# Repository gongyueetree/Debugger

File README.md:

# Debug Studio · CH347 + RP2040

面向 CH347T 四模式硬件与 LA_RP2040 板卡的 Web 下载、调试和测量工作台。包含可独立打开的前端、本机 Python Agent、真实工具后端、演示模式和可选 eve AI 任务助手。

**交付状态：v0.2 开发版。软件测试与六份 RP2040 UF2（V1、V2 各三份）交叉编译已完成，没有连接 CH347 / RP2040 实物进行验收。** 所有真实执行路径都会根据工具退出码、API 返回值和响应长度判定结果，无法连接或缺少依赖时返回错误；不会用演示数据填充真实结果。

## 立即启动

需要 Python 3.10 或更新版本。普通下载、调试和规则助手不需要 Node.js 或模型密钥。

```bash
git clone https://github.com/gongyueetree/Debugger.git
cd Debugger
bash start.sh
```

也可在 GitHub 选择 Code → Download ZIP，解压后按下面的方法启动。

- Windows：解压后双击 `start-windows.bat`。
- macOS / Linux：进入解压目录，执行 `bash start.sh`。
- 首次启动创建 `.venv` 并联网安装 `requirements.txt`。依赖安装失败后，可手动重试 `.venv/bin/python -m pip install -r requirements.txt`（Windows 为 `.venv\Scripts\python.exe`）。
- 自动打开 `http://127.0.0.1:8765` 并通过 URL fragment 完成本次配对，随后清除 fragment。每次服务重启都会生成新配对码。
- 如未自动打开网页，复制终端中的本地地址，点击“连接调试器”并填入本次配对码。
- 在线工作台也能连接此服务；若浏览器限制 HTTPS 页面访问本机 HTTP，直接使用本地网页。不要关闭浏览器安全保护。

仅体验页面、不安装硬件依赖：`python -m bridge.server`。网页默认显示明确标记的演示模式。

启动选项：`python -m bridge.server --port 8765 --no-browser --allow-origin https://your-workbench.example`。来源必须是无路径的精确 origin。

## RP2040 新增功能

- **两种板型**：LA_RP2040 V2（电平转换 1.65–5.5 V、端口保护、16 Pin、兼容官方 Debug Probe 固件，硬件工程和外壳在 [hardware/la-rp2040-v2](hardware/la-rp2040-v2/README.md)）和 V1（3.3 V 直连、12 Pin）。固件各三份，不能混用；V2 逻辑分析深度为 50000 点。V2 尚未打样。
- **MCU 调试 + 串口**：专用 CMSIS-DAP v2 固件，复用网页的 OpenOCD / GDB / UART 工具。
- **8 通道逻辑分析仪**：GP20–GP27，最高配置 20 MSa/s，最多 100000 点，边沿/电平触发、波形缩放、游标、CSV/VCD/PulseView .sr 导出。
- **ADC 数字示波器**：GP26/27/28 中选择一路，最高 500 kSa/s、最多 32768 点，12 bit 原始码、Vpp/RMS、游标、CSV 导出。
- **每种板型三份 UF2**：在「RP2040 固件」页下载，经 BOOTSEL 切换；三个配置不同时运行。完整对应固件源码和许可证一并提供。

输入没有模拟前端或电平转换：信号限定 3.3 V；ADC 输入 0–3.3 V 且不得超过实测参考电压。示波器当前是未校准的单次 ADC 采集，不具备通用示波器的宽输入量程、持续流或硬件模拟触发。详细接线、构建和实板验收见 [docs/RP2040.md](docs/RP2040.md)。RP2040 的 debugprobe 固件不支持 JTAG / SWO，openFPGALoader 继续使用 CH347。

## CH347 功能与要求

| 功能 | 本机后端 | 模式 | 实现范围 |
|---|---|---|---|
| FPGA 扫描、SRAM、配置 Flash | openFPGALoader `ch347_jtag` | 3 | 扫描、文件上传、执行计划、下载日志；实际 FPGA/文件格式以工具支持为准 |
| MCU 烧录与调试 | OpenOCD `ch347` | 3 | STM32F1/F4、RP2040、nRF52、ESP32 配置入口；暂停/继续/单步/复位、寄存器与内存读取、ELF/HEX 烧录；不是全系列兼容承诺 |
| GDB 接入 | OpenOCD | 3 | 本机 `127.0.0.1:3333`；可接 GDB/IDE |
| 串口 | pyserial / HID UART | 0/1/2/3 | 8N1，持续收发、文本与日志；模式 0 可打开两个系统端口；无 UART bootloader 自动下载协议 |
| SPI Flash | flashrom `ch347_spi` | 1 | 识别、备份下载、写入默认校验、独立校验、擦除 |
| I²C | WCH SDK / HID | 1/2 | 100 kHz ACK 扫描、7 bit 地址、1/2 byte 寄存器地址、读写；HID 单事务读 ≤63、寄存器地址与写数据合计 ≤62 bytes |
| SPI 原始事务 | WCH SDK / HID | 1/2 | mode 0–3、MSB first、SCS0、全双工；最多 4096 bytes；选取不高于请求的分频 |
| GPIO | WCH SDK | 3 | GPIO3/5/6 读电平、配置输出；与正在运行的调试/XVC 会话互斥 |
| SVF | OpenOCD | 3 | 单 TAP 链的 SVF 执行，需要 IR 长度与 IDCODE；未实现 BSDL 自动互连测试生成 |
| XVC（实验） | 自带 `bridge.xvc` / pyusb | 3 | 独立 CH347T USB JTAG bitbang，XVC v1.0 getinfo/settck/shift，本机 2542 端口；尚未进行 Vivado/ILA 真机验证 |
| 任务助手 | 本地规则 / 可选 eve | 全部 | 引导工作流，AI 可读取状态和准备计划，不能直接写硬件 |

CH347T 的 PID：模式 0 `55DA`、模式 1 `55DB`、模式 2 `55DC`、模式 3 `55DD`，VID 为 `1A86`。软件模式选择只用于准备任务，实际模式按设备枚举校验。每个系列仅允许连接一个设备，但可同时连接一个 CH347T 与一个 RP2040 并在页面选择；CH347F 的 PID/接口布局未纳入支持。

## 外部工具与驱动

本包不附带厂商 DLL、内核驱动、openFPGALoader、OpenOCD 或 flashrom 的可执行文件。请从各项目/厂商安装适合系统架构的版本，并放入 PATH。

- **openFPGALoader**：`openFPGALoader --list-cables` 应包含 `ch347_jtag`。先运行网页里的 JTAG 扫描。底层使用 libusb；Windows 应按工具文档配置正确的 JTAG USB interface，避免替换 UART interface 的驱动。
- **OpenOCD**：CH347 需要真正包含 `ch347` adapter 的构建；RP2040 使用 `cmsis-dap` bulk adapter；系统发行版的旧版本可能没有。目标脚本需要在它的 scripts 搜索路径中。
- **flashrom**：需要编译进 `ch347_spi` programmer。mode 2 HID 不通过这个 programmer 操作。
- **普通 UART**：安装 WCH 对应串口驱动，使系统枚举 COM / tty 设备。
- **pyusb / XVC**：pyusb 还需要系统 libusb。Linux 按上游文档配置 USB udev 权限；macOS 可用系统包管理器安装 libusb；Windows 需要兼容的 libusb 后端库与接口驱动。
- **HID mode 2**：Python 依赖包含 hidapi 与 ch347api。Linux 需对应 hidraw 权限。macOS 的 HID interface_number 行为没有实物验证；找不到设备时报告失败，不能宣称已跨平台验证。
- **WCH SDK**：用于 mode 1 I²C/SPI 和 mode 3 GPIO。Windows DLL 与 Python 位数必须一致；Linux `.so` 与 CPU 架构必须匹配，并按 WCH 官方说明安装 `/dev/ch34x_pis*` 驱动。

WCH SDK 环境变量示例：

```bash
# Linux，路径以你下载的官方 SDK 和实际节点为准
export CH347_LIBRARY=/absolute/path/libch347.so
export CH347_DEVICE_PATH=/dev/ch34x_pis0
bash start.sh
```

```powershell
# Windows PowerShell
$env:CH347_LIBRARY = 'C:\WCH\CH347DLLA64.dll'
$env:CH347_DEVICE_INDEX = '0'
.\start-windows.bat
```

SDK 动态库名称可能随包变化，请填写实际文件；不自动下载 DLL。Linux WCH 字符设备驱动与 libusb 的接口占用可能冲突，切换后端前应停止占用者。SDK ctypes 绑定分别处理 Windows index 与 Linux fd，并使用 `_pack_=1`、固定宽度整数，SPIConfig 为 20 bytes。

## 推荐验收顺序

1. 不接目标板，分别以四种硬件模式上电；连接工作台，确认 PID、版本、串口与驱动识别结果。
2. UART 用 TX/RX 回环测试；模式 0 的两个端口分别验证。新板的 UART0 复用接线以原理图为准。
3. 使用已知 I²C 器件，只读器件标识；随后在可恢复寄存器测试写入。检查模式 1 / 2 ACK 和返回长度。
4. 用独立测试 Flash 进行识别、完整备份、擦除、写入、再次读回比较 SHA-256。
5. JTAG 在 1 MHz 读取稳定 IDCODE；FPGA 先 SRAM 测试设计，再测试配置 Flash 掉电重载。
6. 对支持的 MCU 测试下载校验、复位、暂停、单步、寄存器、内存与外部 GDB。
7. 最后验证 GPIO 与实验性 XVC；观察实际波形、TDO 时序和 Vivado/ILA 行为。

不能用这个软件补足硬件缺失：+3V3 是输出而不是 VTref；若新版要调试 1.8 V 等目标需对应电平转换和方向设计。CH347T 2.41 无原生 SWD，4.41/5.44 有相关限制；本实现 SWD 保守限制 1 MHz。它不是示波器、逻辑分析仪或自动支持任意 MCU 的通用探针。

## 执行与数据策略

- Agent 仅监听 `127.0.0.1`。API 使用启动时随机 Bearer token，检查 Host 和精确 Origin，阻止外网页跨站调用与 DNS rebinding。
- 文件只传给本机 Agent。最多 64 MiB；内部随机文件名；执行前重新比对 SHA-256。上传文件不能成为任意配置脚本或 shell 命令。
- 所有任务先生成最多 5 分钟有效的计划。改变目标状态的操作需确认；同一个计划重复提交不会再次执行。
- 子进程全部参数化调用、无 shell；目标配置为白名单。总线事务在可终止的独立进程中执行；硬件任务互斥，失败不自动重试。
- 服务重启时把进行中的任务标记为 interrupted，绝不自动重放；目标可能处于部分写入状态，需要读回或校验。
- 文件、备份和最近 200 个任务日志保存在用户目录 `.ch347-studio`。程序不会自动删除固件；需要时在服务停止后由用户清理。历史记录会持久化，当前内存中的文件下载映射在服务重启后失效，文件本体仍留在目录内。
- 串口接收记录保留最近 3000 条；操作日志每任务最近 1500 行。关闭网页不会停止已启动的后台会话；使用“断开并停止会话”或在终端 Ctrl+C。
- 非 AI 路径不发送固件或设备数据到模型。启用 AI 后，用户问题和工具返回的设备状态/计划会发送给配置的模型服务；文件内容仍不作为模型附件发送。

## GDB 示例

在网页启动 MCU 调试后：

```gdb
target extended-remote 127.0.0.1:3333
monitor halt
info registers
x/16wx 0x20000000
```

若在外部 GDB 操作目标，应避免同时点击网页调试控制。自定义目标需要在 `bridge/core.py` 的 TARGETS 白名单中添加经过核实的脚本，并更新前端列表；当前网页不接受任意 OpenOCD 配置文件。

## 可选 AI Agent

普通功能完全不依赖模型。`agent-runtime/` 使用 eve，默认模型保留 scaffold 的 `openai/gpt-6-luna-fast`，工具只有读取状态和准备计划；禁用默认 shell、文件和网页工具。

1. 使用 Node.js 24，在 `agent-runtime` 执行 `npm ci`。
2. 在本机配置可用的 AI Gateway 凭据（如 `AI_GATEWAY_API_KEY`），不要放进网页或提交到仓库。此交付未配置凭据，未执行付费模型调用。
3. 启动 Python Agent 前设置 `CH347_EVE_URL=http://127.0.0.1:2000`。启动 Python Agent 后，从终端获得本次配对码。
4. 在 **eve 所在终端** 设置 `CH347_BRIDGE_URL=http://127.0.0.1:8765` 和 `CH347_BRIDGE_TOKEN=本次配对码`，执行 `npx eve dev --no-ui`。若开发服务器端口不是 2000，更新 CH347_EVE_URL 并重新启动 Python Agent，同时更新 eve 的配对码。
5. 工作台刷新连接状态后显示 “EVE AI · 已配置”。这里只表示环境变量已设置；网络、密钥或模型失败时会明确报错。建议先运行 `npm run typecheck` 和 `npm run build`。

AI 返回的是建议与计划文本；最终仍需到相应模块确认执行。Agent 端模型调用不拥有 `/api/execute` 工具，不能绕过网页确认。

## 代码与测试

```text
dist/                独立网页：HTML / CSS / JavaScript
bridge/server.py     localhost HTTP、配对、CORS、上传与下载
bridge/core.py       计划验证、任务互斥、进程、OpenOCD/FPGA/Flash/UART
bridge/bus.py        WCH SDK ABI 与 HID 总线适配
bridge/xvc.py        实验性 CH347T 原始 USB XVC
agent-runtime/       可选 eve AI Agent，typed tools
requirements.txt     Python 依赖
start.sh             macOS / Linux 启动
start-windows.bat    Windows 启动
tests/               硬件隔离的软件测试
```

运行 `python -m unittest discover -s tests -v`。57 项 Python 测试覆盖 RP2040 采集协议、导出、UF2 校验，以及 CH347 的模式、版本、目标配置、文件完整性、计划确认与去重、子进程失败/取消、鉴权/Origin/Host、XVC 向量分包与 TCP 协议。测试使用受控模拟硬件，不能替代真机验收。

运行 `node --test tests/test_waveform.js` 可执行 4 项波形视图回归测试（测试需要 Node.js）。前端已通过浏览器检查缩放按钮、滚轮缩放、滑杆和波形拖动、游标保留，以及导航、计划生成、演示执行与记录；SHA-256 fallback 使用 4 个标准实现对照向量校验。eve 类型检查与生产构建通过，模型调用未测试。

## 参考来源

- WCH CH347 官方资料：https://www.wch.cn/products/CH347.html
- WCH Linux SDK：https://github.com/WCHSoftGroup/ch341par_linux
- WCH Linux ABI：https://github.com/WCHSoftGroup/ch341par_linux/blob/main/demo/ch347/ch347_lib.h
- openFPGALoader：https://github.com/trabucayre/openFPGALoader
- CH347 USB 协议核对：https://github.com/trabucayre/openFPGALoader/blob/master/src/ch347jtag.cpp
- XVC 支持范围核对：https://github.com/trabucayre/openFPGALoader/blob/master/src/xvc_server.cpp
- OpenOCD：https://github.com/openocd-org/openocd
- flashrom：https://github.com/flashrom/flashrom
- HID Python 实现：https://github.com/i2cy/CH347-HIDAPI

特别说明：openFPGALoader 支持 `ch347_jtag` 下载；经检查其 XVC 构造器尚未接入 CH347，且该实现未使用传入 IP 绑定地址。因此本项目没有直接调用 `openFPGALoader --xvc -c ch347_jtag`，而实现了只监听 loopback 的独立 XVC 后端。HID I²C 加入超时、返回长度与帧检查；HID GPIO 目前未开放。

## 生成完整启动包

```bash
python package_release.py dist/CH347_Debug_Studio.zip
```

这会生成网页“连接设置”中可下载的完整启动包；Git 仓库不重复提交这个生成文件。`dist/firmware/` 已包含三份专用 UF2、版本校验清单和完整对应源码包，克隆后即可使用。

## 工具汇总与硬件可视化

左侧「工具汇总」可下载两块板的原始 KiCad 9 工程，并在线查看带图纸外框和标题栏的原理图、PCB 双层叠加 / 正反面及可旋转的 3D 装配模型。PCB 可点击走线、焊盘或过孔，高亮整个网络并显示名称和连接的管脚。板卡图片与 3D 均保留原始管脚丝印；各功能页显示实际 J2 脚号、板上丝印和当前功能，随 ADC、GPIO、UART 与总线选择更新。详见 [硬件资料与重建说明](docs/HARDWARE.md)。

验证：`python -m unittest discover -s tests -v`（57 项），`node --test tests/test_waveform.js tests/test_hardware.js tests/test_pcb_viewer.js`（13 项）。硬件资料校验包括原文件哈希、正反面焊盘、丝印对应、引脚映射与本地静态资源类型。

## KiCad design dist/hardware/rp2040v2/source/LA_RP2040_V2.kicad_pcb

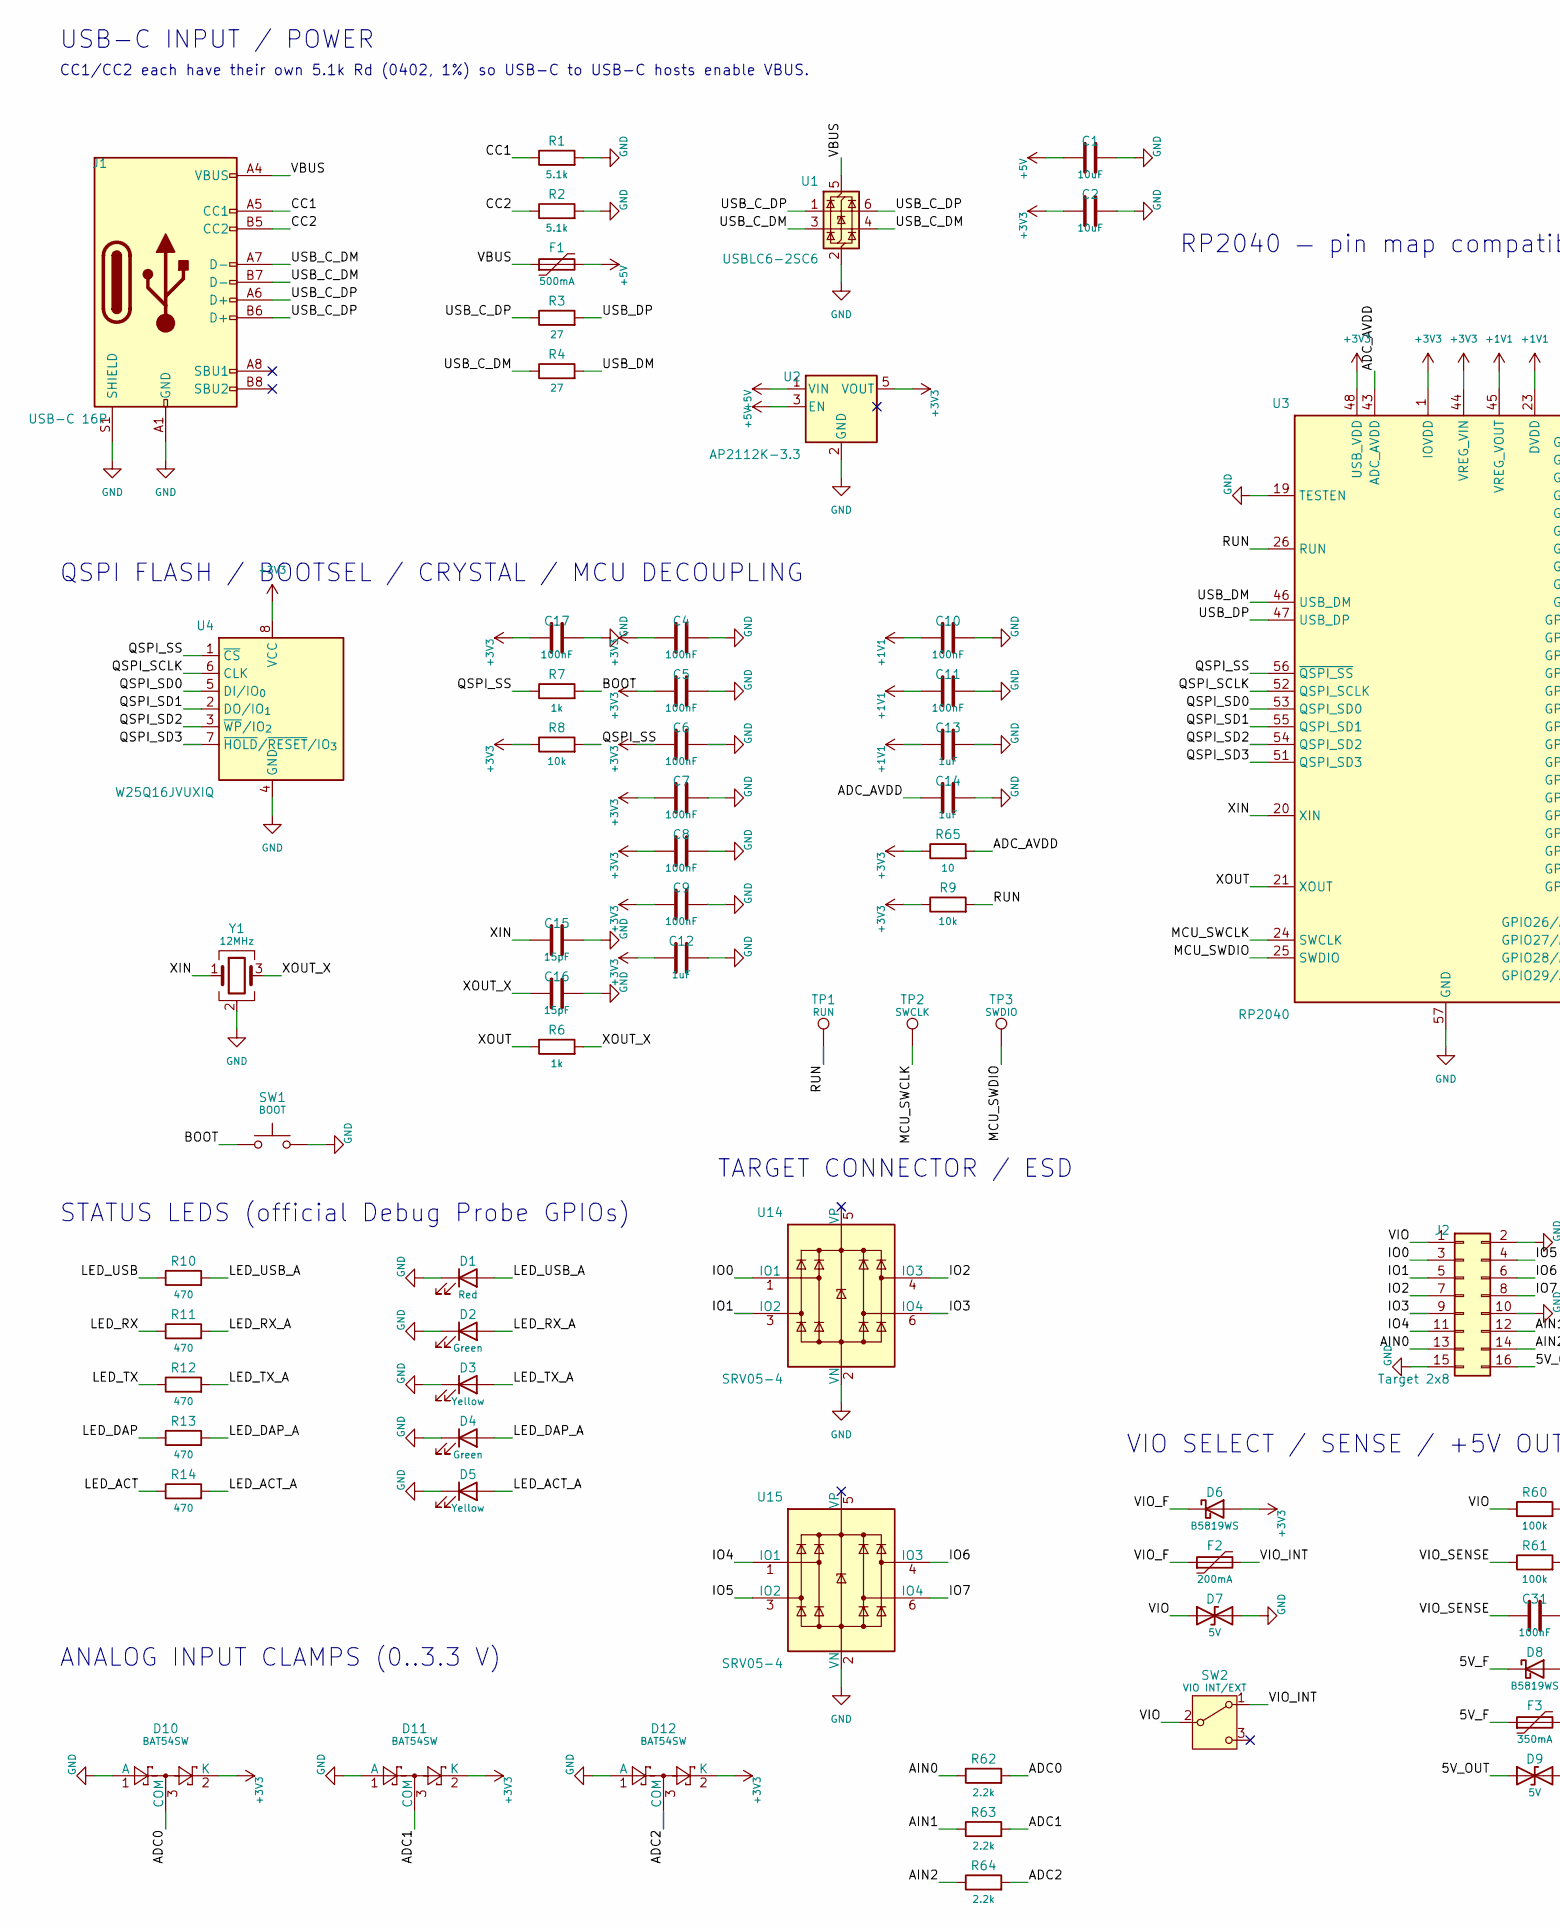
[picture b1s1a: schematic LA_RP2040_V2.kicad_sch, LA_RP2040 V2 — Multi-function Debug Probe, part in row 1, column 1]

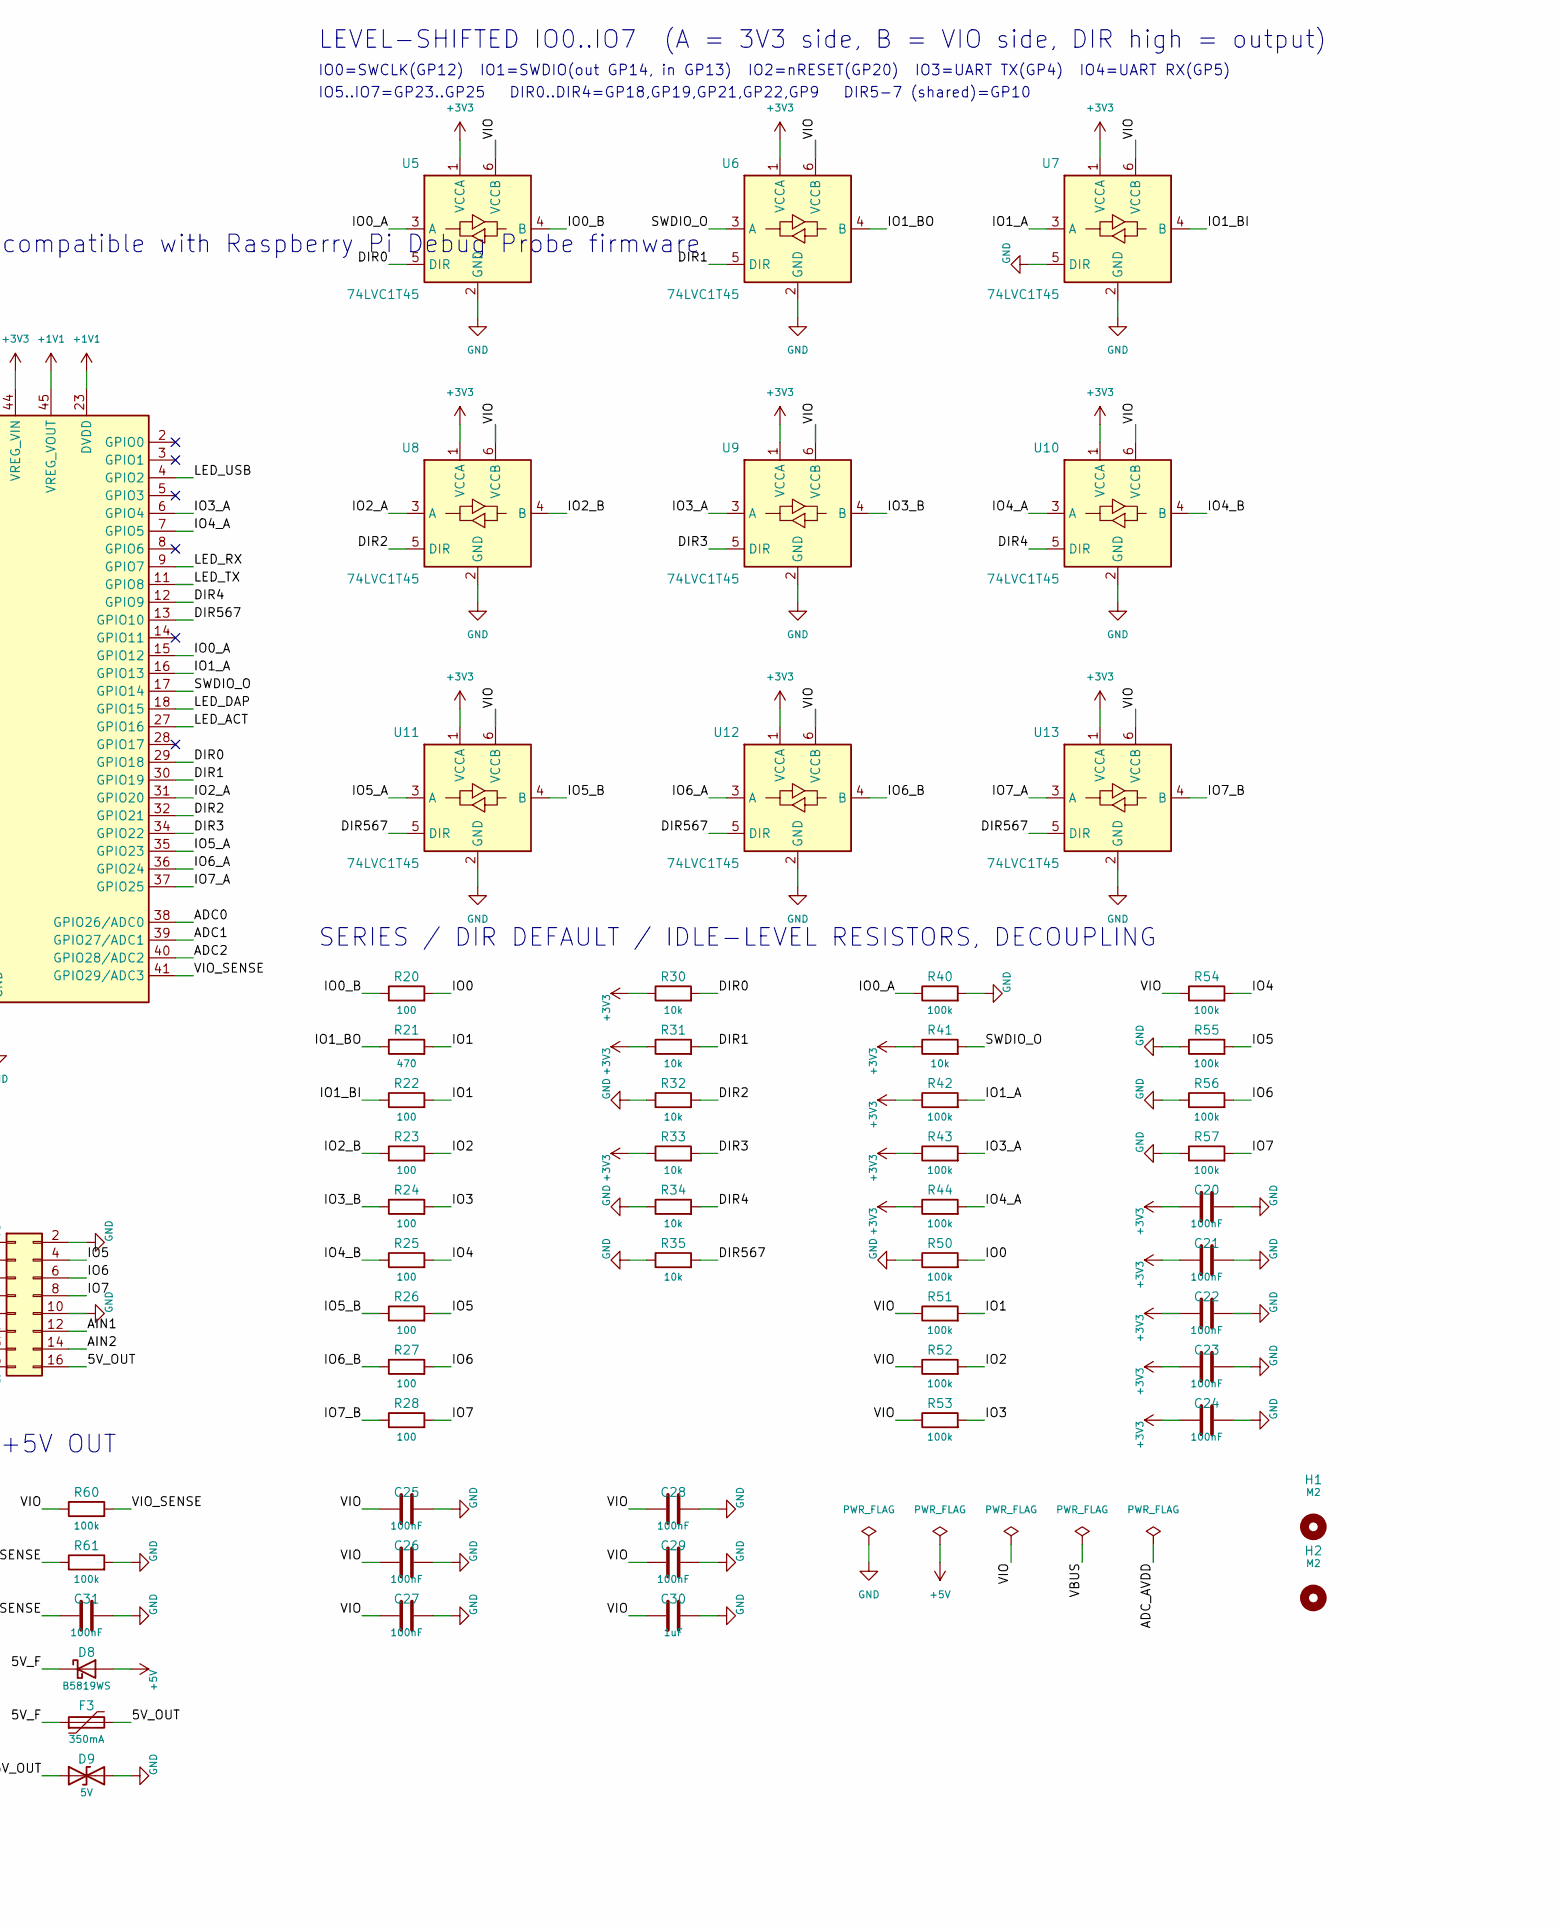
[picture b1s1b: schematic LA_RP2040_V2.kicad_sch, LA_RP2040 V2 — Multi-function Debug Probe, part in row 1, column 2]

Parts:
C1, C2: 10uF; C_0603_1608Metric; MPN 0603 10uF X5R/X7R (15pF: C0G)
C4, C5, C6, C7, C8, C9, C10, C11, C17, C20, C21, C22, C23, C24, C25, C26, C27, C28, C29, C31: 100nF; C_0402_1005Metric; MPN 0402 100nF X5R/X7R (15pF: C0G)
C12, C13, C14, C30: 1uF; C_0402_1005Metric; MPN 0402 1uF X5R/X7R (15pF: C0G)
C15, C16: 15pF; C_0402_1005Metric; MPN 0402 15pF X5R/X7R (15pF: C0G)
D1: Red; LED_0603_1608Metric; MPN 0603 LED Red
D2, D4: Green; LED_0603_1608Metric; MPN 0603 LED Green
D3, D5: Yellow; LED_0603_1608Metric; MPN 0603 LED Yellow
D6, D8: B5819WS; D_SOD-323; MPN B5819WS (SOD-323)
D7, D9: 5V; D_SOD-323; MPN PESD5V0S1BA (SOD-323)
D10, D11, D12: BAT54SW; SOT-323_SC-70; MPN BAT54SW (SOT-323)
F1: 500mA; Fuse_0805_2012Metric; MPN 0805 PTC 0.5A hold / 6V (e.g. SMD0805P0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
F2: 200mA; Fuse_0603_1608Metric; MPN 0603 PTC 0.2A hold / 6V
F3: 350mA; Fuse_0603_1608Metric; MPN 0603 PTC 0.35A hold / 6V
H1, H2: M2; MountingHole_2.2mm_M2
J1: USB-C 16P; USB_C_Receptacle_HRO_TYPE-C-31-M-12; MPN HRO TYPE-C-31-M-12
J2: Target 2x8; PinHeader_2x08_P2.54mm_EdgeMount; MPN 2x8 2.54 mm straight pin header, stradd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
R1, R2: 5.1k; R_0402_1005Metric; MPN 0402 5.1k 1%
R3, R4: 27; R_0402_1005Metric; MPN 0402 27 1%
R6, R7: 1k; R_0402_1005Metric; MPN 0402 1k 1%
R8, R9, R30, R31, R32, R33, R34, R35, R41: 10k; R_0402_1005Metric; MPN 0402 10k 1%
R10, R11, R12, R13, R14, R21: 470; R_0402_1005Metric; MPN 0402 470 1%
R20, R22, R23, R24, R25, R26, R27, R28: 100; R_0402_1005Metric; MPN 0402 100 1%
R40, R42, R43, R44, R50, R51, R52, R53, R54, R55, R56, R57, R60, R61: 100k; R_0402_1005Metric; MPN 0402 100k 1%
R62, R63, R64: 2.2k; R_0402_1005Metric; MPN 0402 2.2k 1%
R65: 10; R_0402_1005Metric; MPN 0402 10 1%
SW1: BOOT; SW_SPST_B3U-1000P; MPN Omron B3U-1000P
SW2: VIO INT/EXT; SW_SPDT_Shouhan_MSK12C02; MPN Shouhan MSK-12C02
TP1: RUN; TestPoint_Pad_D1.0mm
TP2: SWCLK; TestPoint_Pad_D1.0mm
TP3: SWDIO; TestPoint_Pad_D1.0mm
U1: USBLC6-2SC6; SOT-23-6; MPN USBLC6-2SC6
U2: AP2112K-3.3; SOT-23-5; MPN AP2112K-3.3TRG1
U3: RP2040; QFN-56-1EP_7x7mm_P0.4mm_EP3.2x3.2mm; MPN RP2040
U4: W25Q16JVUXIQ; Winbond_USON-8-1EP_3x2mm_P0.5mm_EP0.2x1.6mm; MPN W25Q16JVUXIQ
U5, U6, U7, U8, U9, U10, U11, U12, U13: 74LVC1T45; SOT-363_SC-70-6; MPN SN74LVC1T45DCKR
U14, U15: SRV05-4; SOT-23-6; MPN SRV05-4 (SOT-23-6)
Y1: 12MHz; Crystal_SMD_3225-4Pin_3.2x2.5mm; MPN 12 MHz 3225 CL=10..12pF (e.g. ABM8-272-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

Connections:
+1V1: C10.1, C11.1, C13.1, U3.23 (DVDD), U3.45 (VREG_VOUT), U3.50 (DVDD)
+3V3: C2.1, C4.1, C5.1, C6.1, C7.1, C8.1, C9.1, C12.1, C17.1, C20.1, C21.1, C22.1, C23.1, C24.1, D6.2 (A), D10.2 (K), D11.2 (K), D12.2 (K), R8.1, R9.1, R30.1, R31.1, R33.1, R41.1, R42.1, R43.1, R44.1, R65.1, U2.5 (VOUT), U3.1 (IOVDD), U3.10 (IOVDD), U3.22 (IOVDD), U3.33 (IOVDD), U3.42 (IOVDD), U3.44 (VREG_VIN), U3.48 (USB_VDD), U3.49 (IOVDD), U4.8 (VCC), U5.1 (VCCA), U6.1 (VCCA), U7.1 (VCCA), U8.1 (VCCA), U9.1 (VCCA), U10.1 (VCCA), U11.1 (VCCA), U12.1 (VCCA), U13.1 (VCCA)
+5V: C1.1, D8.2 (A), F1.2, U2.1 (VIN), U2.3 (EN)
/5V_F: D8.1 (K), F3.1
/5V_OUT: D9.1 (A1), F3.2, J2.16
/ADC0: D10.3 (COM), R62.2, U3.38 (GPIO26/ADC0)
/ADC1: D11.3 (COM), R63.2, U3.39 (GPIO27/ADC1)
/ADC2: D12.3 (COM), R64.2, U3.40 (GPIO28/ADC2)
/ADC_AVDD: C14.1, R65.2, U3.43 (ADC_AVDD)
/AIN0: J2.13, R62.1
/AIN1: J2.12, R63.1
/AIN2: J2.14, R64.1
/BOOT: R7.2, SW1.1
/CC1: J1.A5 (CC1), R1.1
/CC2: J1.B5 (CC2), R2.1
/DIR0: R30.2, U3.29 (GPIO18), U5.5 (DIR)
/DIR1: R31.2, U3.30 (GPIO19), U6.5 (DIR)
/DIR2: R32.2, U3.32 (GPIO21), U8.5 (DIR)
/DIR3: R33.2, U3.34 (GPIO22), U9.5 (DIR)
/DIR4: R34.2, U3.12 (GPIO9), U10.5 (DIR)
/DIR567: R35.2, U3.13 (GPIO10), U11.5 (DIR), U12.5 (DIR), U13.5 (DIR)
/IO0: J2.3, R20.2, R50.2, U14.1 (IO1)
/IO0_A: R40.1, U3.15 (GPIO12), U5.3 (A)
/IO0_B: R20.1, U5.4 (B)
/IO1: J2.5, R21.2, R22.2, R51.2, U14.3 (IO2)
/IO1_A: R42.2, U3.16 (GPIO13), U7.3 (A)
/IO1_BI: R22.1, U7.4 (B)
/IO1_BO: R21.1, U6.4 (B)
/IO2: J2.7, R23.2, R52.2, U14.4 (IO3)
/IO2_A: U3.31 (GPIO20), U8.3 (A)
/IO2_B: R23.1, U8.4 (B)
/IO3: J2.9, R24.2, R53.2, U14.6 (IO4)
/IO3_A: R43.2, U3.6 (GPIO4), U9.3 (A)
/IO3_B: R24.1, U9.4 (B)
/IO4: J2.11, R25.2, R54.2, U15.1 (IO1)
/IO4_A: R44.2, U3.7 (GPIO5), U10.3 (A)
/IO4_B: R25.1, U10.4 (B)
/IO5: J2.4, R26.2, R55.2, U15.3 (IO2)
/IO5_A: U3.35 (GPIO23), U11.3 (A)
/IO5_B: R26.1, U11.4 (B)
/IO6: J2.6, R27.2, R56.2, U15.4 (IO3)
/IO6_A: U3.36 (GPIO24), U12.3 (A)
/IO6_B: R27.1, U12.4 (B)
/IO7: J2.8, R28.2, R57.2, U15.6 (IO4)
/IO7_A: U3.37 (GPIO25), U13.3 (A)
/IO7_B: R28.1, U13.4 (B)
/LED_ACT: R14.1, U3.27 (GPIO16)
/LED_ACT_A: D5.2 (A), R14.2
/LED_DAP: R13.1, U3.18 (GPIO15)
/LED_DAP_A: D4.2 (A), R13.2
/LED_RX: R11.1, U3.9 (GPIO7)
/LED_RX_A: D2.2 (A), R11.2
/LED_TX: R12.1, U3.11 (GPIO8)
/LED_TX_A: D3.2 (A), R12.2
/LED_USB: R10.1, U3.4 (GPIO2)
/LED_USB_A: D1.2 (A), R10.2
/MCU_SWCLK: TP2.1, U3.24 (SWCLK)
/MCU_SWDIO: TP3.1, U3.25 (SWDIO)
/QSPI_SCLK: U3.52 (QSPI_SCLK), U4.6 (CLK)
/QSPI_SD0: U3.53 (QSPI_SD0), U4.5 (DI/IO_{0})
/QSPI_SD1: U3.55 (QSPI_SD1), U4.2 (DO/IO_{1})
/QSPI_SD2: U3.54 (QSPI_SD2), U4.3 (~WP/IO_{2})
/QSPI_SD3: U3.51 (QSPI_SD3), U4.7 (~HOLD/~RESET/IO_{3})
/QSPI_SS: R7.1, R8.2, U3.56 (~QSPI_SS), U4.1 (~CS)
/RUN: R9.2, TP1.1, U3.26 (RUN)
/SWDIO_O: R41.2, U3.17 (GPIO14), U6.3 (A)
/USB_C_DM: J1.A7 (D-), J1.B7 (D-), R4.1, U1.3 (I/O2), U1.4 (I/O2)
/USB_C_DP: J1.A6 (D+), J1.B6 (D+), R3.1, U1.1 (I/O1), U1.6 (I/O1)
/USB_DM: R4.2, U3.46 (USB_DM)
/USB_DP: R3.2, U3.47 (USB_DP)
/VBUS: F1.1, J1.A4 (VBUS), J1.A9 (VBUS), J1.B4 (VBUS), J1.B9 (VBUS), U1.5 (VBUS)
/VIO_F: D6.1 (K), F2.1
/VIO_INT: F2.2, SW2.1 (A)
/VIO_SENSE: C31.1, R60.2, R61.1, U3.41 (GPIO29/ADC3)
/XIN: C15.1, U3.20 (XIN), Y1.1
/XOUT: R6.1, U3.21 (XOUT)
/XOUT_X: C16.1, R6.2, Y1.3
GND: C1.2, C2.2, C4.2, C5.2, C6.2, C7.2, C8.2, C9.2, C10.2, C11.2, C12.2, C13.2, C14.2, C15.2, C16.2, C17.2, C20.2, C21.2, C22.2, C23.2, C24.2, C25.2, C26.2, C27.2, C28.2, C29.2, C30.2, C31.2, D1.1 (K), D2.1 (K), D3.1 (K), D4.1 (K), D5.1 (K), D7.2 (A2), D9.2 (A2), D10.1 (A), D11.1 (A), D12.1 (A), J1.A1 (GND), J1.A12 (GND), J1.B1 (GND), J1.B12 (GND), J1.S1 (SHIELD), J2.2, J2.10, J2.15, R1.2, R2.2, R32.1, R34.1, R35.1, R40.2, R50.1, R55.1, R56.1, R57.1, R61.2, SW1.2, U1.2 (GND), U2.2 (GND), U3.19 (TESTEN), U3.57 (GND), U4.4 (GND), U5.2 (GND), U6.2 (GND), U7.2 (GND), U7.5 (DIR), U8.2 (GND), U9.2 (GND), U10.2 (GND), U11.2 (GND), U12.2 (GND), U13.2 (GND), U14.2 (VN), U15.2 (VN), Y1.2 (G), Y1.4 (G)
VIO: C25.1, C26.1, C27.1, C28.1, C29.1, C30.1, D7.1 (A1), J2.1, R51.1, R52.1, R53.1, R54.1, R60.1, SW2.2 (B), U5.6 (VCCB), U6.6 (VCCB), U7.6 (VCCB), U8.6 (VCCB), U9.6 (VCCB), U10.6 (VCCB), U11.6 (VCCB), U12.6 (VCCB), U13.6 (VCCB)

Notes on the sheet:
USB-C INPUT / POWER
QSPI FLASH / BOOTSEL / CRYSTAL / MCU DECOUPLING
STATUS LEDS (official Debug Probe GPIOs)
RP2040 — pin map compatible with Raspberry Pi Debug Probe firmware
LEVEL-SHIFTED IO0..IO7 (A = 3V3 side, B = VIO side, DIR high = output)
SERIES / DIR DEFAULT / IDLE-LEVEL RESISTORS, DECOUPLING
TARGET CONNECTOR / ESD
VIO SELECT / SENSE / +5V OUT
ANALOG INPUT CLAMPS (0..3.3 V)
IO0=SWCLK(GP12) IO1=SWDIO(out GP14, in GP13) IO2=nRESET(GP20) IO3=UART TX(GP4) IO4=UART RX(GP5)
IO5..IO7=GP23..GP25 DIR0..DIR4=GP18,GP19,GP21,GP22,GP9 DIR5-7 (shared)=GP10
CC1/CC2 each have their own 5.1k Rd (0402, 1%) so USB-C to USB-C hosts enable VBUS.

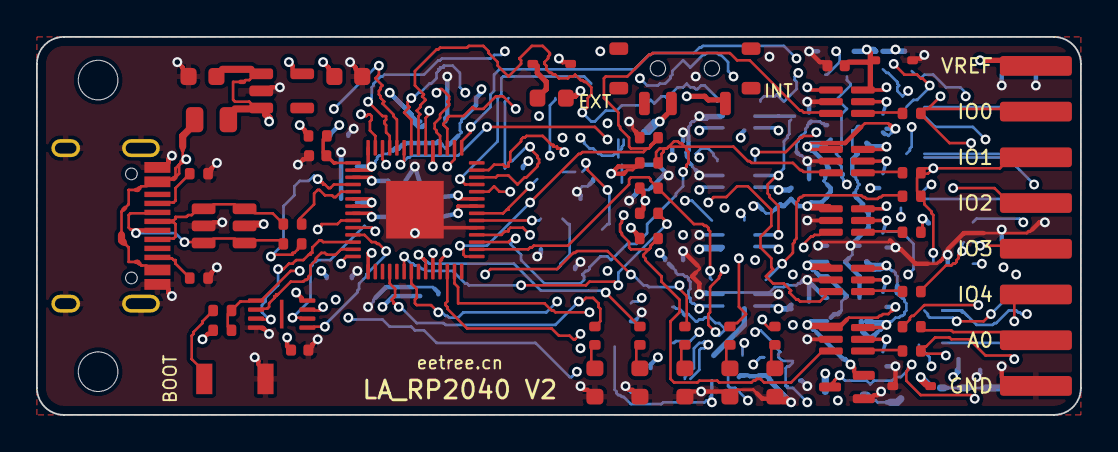
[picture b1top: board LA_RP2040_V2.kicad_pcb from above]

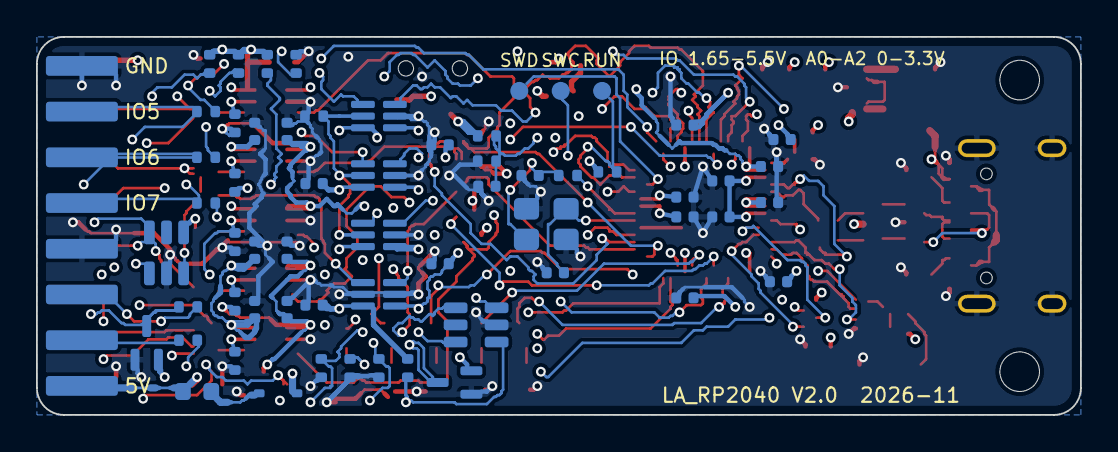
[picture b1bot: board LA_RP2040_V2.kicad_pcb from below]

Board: 4 copper layers, 58.0 x 21.0 mm, 115 parts (60 on the bottom side), 79 nets.

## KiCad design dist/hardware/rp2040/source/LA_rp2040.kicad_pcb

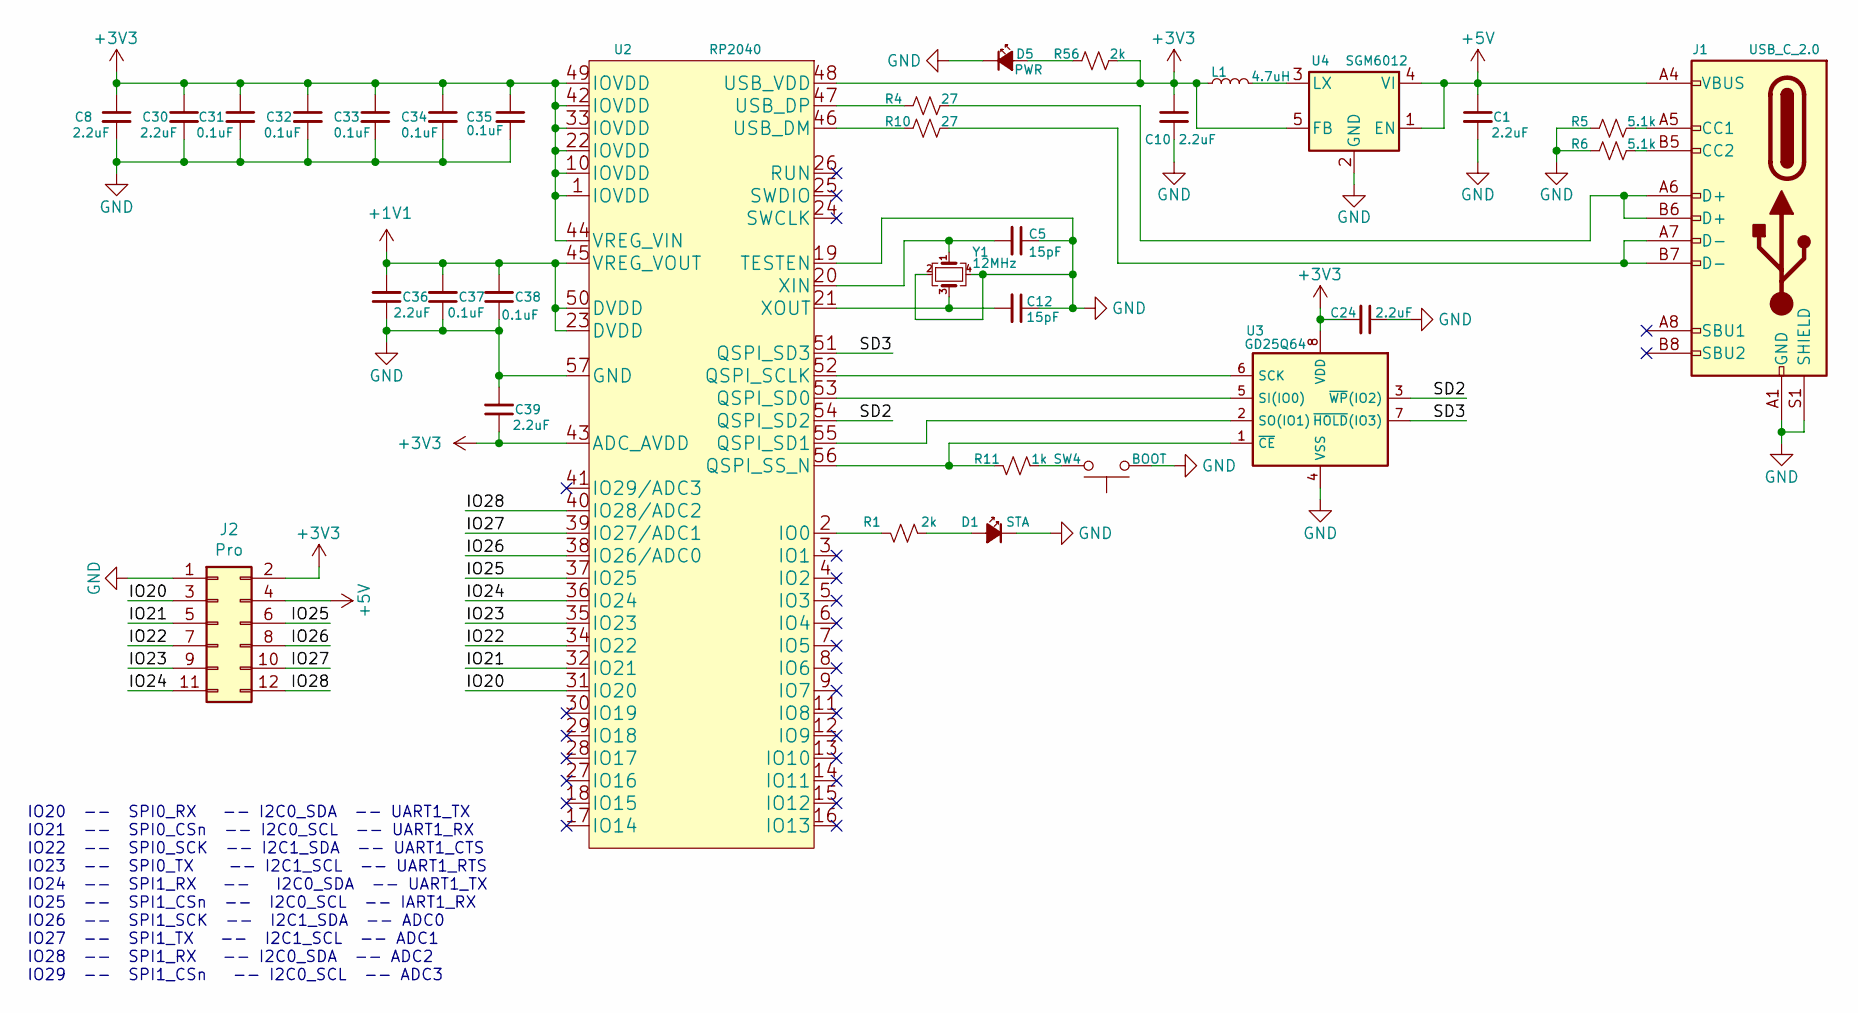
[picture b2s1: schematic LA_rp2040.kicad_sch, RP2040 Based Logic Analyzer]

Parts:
C1, C8, C24, C30, C36, C39: 2.2uF; C_0402_1005Metric
C5, C12: 15pF; C_0201_0603Metric
C10: 2.2uF; C_0603_1608Metric
C31, C32, C33, C34, C35, C37, C38: 0.1uF; C_0201_0603Metric
D1: STA; LED_0603_1608Metric
D5: PWR; LED_0603_1608Metric
J1: USB_C_2.0; USB_C_Receptacle_Palconn_UTC16-G
J2: Pro; PinHeader_2x06_P2.54mm_Horizontal_SMD
L1: 4.7uH; L_0603_1608Metric
R1, R56: 2k; R_0201_0603Metric
R4, R10: 27; R_0201_0603Metric
R5, R6: 5.1k; R_0201_0603Metric
R11: 1k; R_0201_0603Metric
SW4: BOOT; SW_SPST_B3U-1000P
U2: RP2040
U3: GD25Q64; SO-8_3.9x4.9mm_P1.27mm; MPN 1040310811
U4: SGM6012; SOT-23-5
Y1: 12MHz; Crystal_SMD_3225-4Pin_3.2x2.5mm

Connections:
+1V1: C36.2, C37.2, C38.2, U2.23 (DVDD), U2.45 (VREG_VOUT), U2.50 (DVDD)
+3V3: C8.1, C10.1, C24.2, C30.1, C31.1, C32.1, C33.1, C34.1, C35.1, C39.1, J2.2, L1.1, R56.1, U2.1 (IOVDD), U2.10 (IOVDD), U2.22 (IOVDD), U2.33 (IOVDD), U2.42 (IOVDD), U2.43 (ADC_AVDD), U2.44 (VREG_VIN), U2.48 (USB_VDD), U2.49 (IOVDD), U3.8 (VDD), U4.5 (FB)
+5V: C1.1, J1.A4 (VBUS), J1.A9 (VBUS), J1.B4 (e), J1.B9 (e), J2.4, U4.1 (EN), U4.4 (VI)
/IO20: J2.3, U2.31 (IO20)
/IO21: J2.5, U2.32 (IO21)
/IO22: J2.7, U2.34 (IO22)
/IO23: J2.9, U2.35 (IO23)
/IO24: J2.11, U2.36 (IO24)
/IO25: J2.6, U2.37 (IO25)
/IO26: J2.8, U2.38 (IO26/ADC0)
/IO27: J2.10, U2.39 (IO27/ADC1)
/IO28: J2.12, U2.40 (IO28/ADC2)
/SD2: U2.54 (QSPI_SD2), U3.3 (~WP(IO2))
/SD3: U2.51 (QSPI_SD3), U3.7 (~HOLD(IO3))
GND: C1.2, C5.1, C8.2, C10.2, C12.1, C24.1, C30.2, C31.2, C32.2, C33.2, C34.2, C35.2, C36.1, C37.1, C38.1, C39.2, D1.1 (K), D5.1 (K), J1.A1 (GND), J1.A12 (GND), J1.B1 (GND), J1.B12 (GND), J1.S1 (SHIELD), J2.1, R5.2, R6.2, SW4.2, U2.19 (TESTEN), U2.57 (GND), U3.4 (VSS), U4.2 (GND), Y1.2, Y1.4
unnamed: C5.2, U2.20 (XIN), Y1.1
unnamed: C12.2, U2.21 (XOUT), Y1.3
unnamed: D1.2 (A), R1.2
unnamed: D5.2 (A), R56.2
unnamed: J1.A5 (CC1), R5.1
unnamed: J1.A6 (D+), J1.B6 (D+), R4.1
unnamed: J1.A7 (D-), J1.B7 (D-), R10.1
unnamed: J1.B5 (CC2), R6.1
unnamed: L1.2, U4.3 (LX)
unnamed: R1.1, U2.2 (IO0)
unnamed: R4.2, U2.47 (USB_DP)
unnamed: R10.2, U2.46 (USB_DM)
unnamed: R11.1, U2.56 (QSPI_SS_N), U3.1 (~CE)
unnamed: R11.2, SW4.1
unnamed: U2.52 (QSPI_SCLK), U3.6 (SCK)
unnamed: U2.53 (QSPI_SD0), U3.5 (SI(IO0))
unnamed: U2.55 (QSPI_SD1), U3.2 (SO(IO1))

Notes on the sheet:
IO20 -- SPI0_RX -- I2C0_SDA -- UART1_TX IO21 -- SPI0_CSn -- I2C0_SCL -- UART1_RX IO22 -- SPI0_SCK -- I2C1_SDA -- UART1_CTS IO23 -- SPI0_TX -- I2C1_SCL -- UART1_RTS IO24 -- SPI1_RX -- I2C0_SDA -- UART1_TX IO25 -- SPI1_CSn -- I2C0_SCL -- IART1_RX IO26 -- SPI1_SCK -- I2C1_SDA -- ADC0 IO27 -- SPI1_TX -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

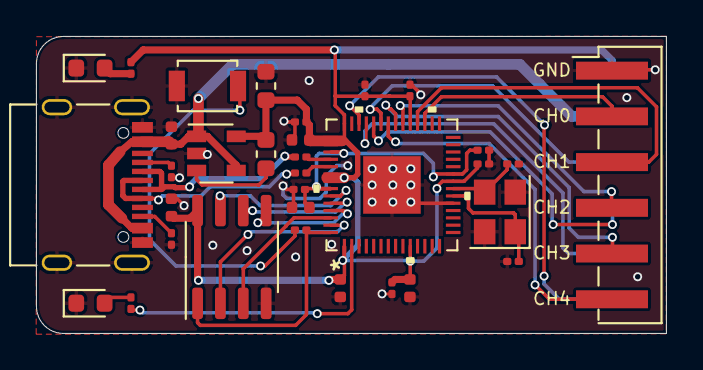
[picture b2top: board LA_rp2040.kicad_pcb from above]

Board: 2 copper layers, 35.0 x 16.5 mm, 33 parts (0 on the bottom side), 32 nets.

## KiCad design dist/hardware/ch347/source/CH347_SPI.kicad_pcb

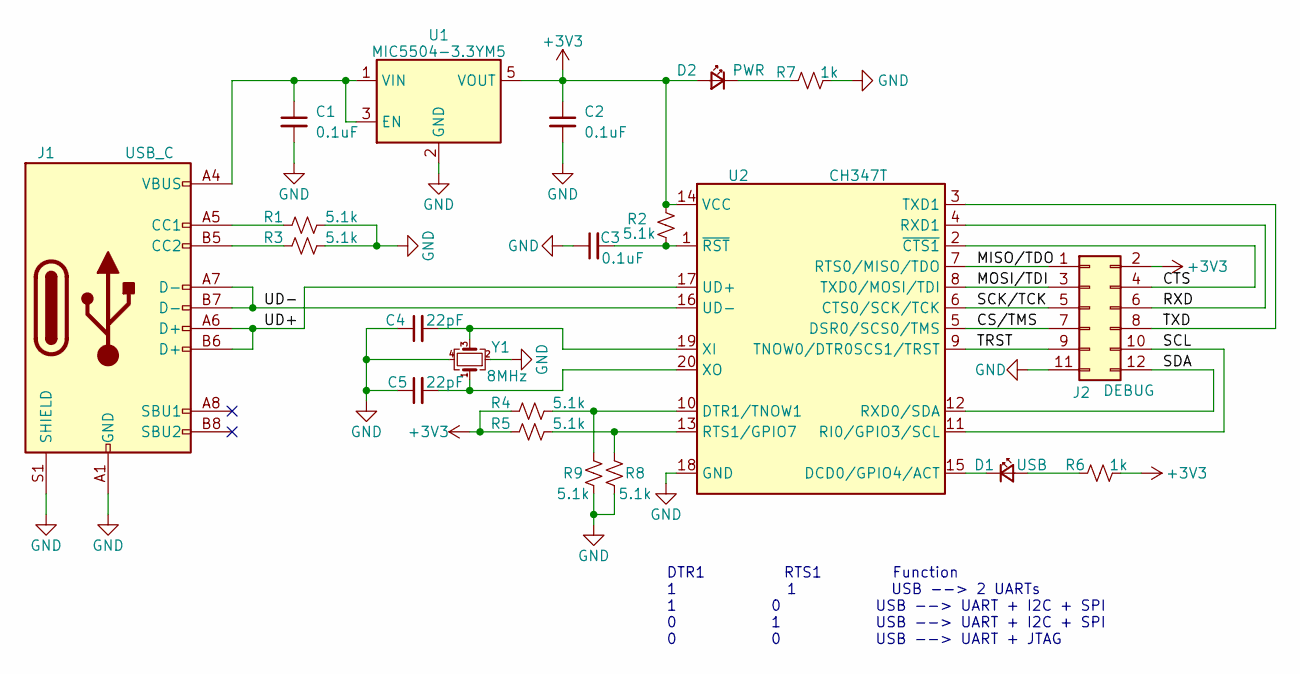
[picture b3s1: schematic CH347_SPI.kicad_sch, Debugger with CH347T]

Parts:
C1, C2, C3: 0.1uF; C_0603_1608Metric
C4, C5: 22pF; C_0603_1608Metric
D1: USB; LED_0603_1608Metric
D2: PWR; LED_0603_1608Metric
J1: USB_C; USB_C_Receptacle_Palconn_UTC16-G
J2: DEBUG; PinHeader_2x06_P2.54mm_Horizontal_SMD
R1, R2, R3, R4, R5, R8, R9: 5.1k; R_0603_1608Metric
R6, R7: 1k; R_0603_1608Metric
U1: MIC5504-3.3YM5; SOT-23-5
U2: CH347T; TSSOP-20_4.4x6.5mm_P0.65mm
Y1: 8MHz; Crystal_SMD_Abracon_ABM8G-4Pin_3.2x2.5mm

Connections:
+3V3: C2.1, D2.2 (A), J2.2, R2.2, R4.1, R5.1, R6.2, U1.5 (VOUT), U2.14 (VCC)
/CS/TMS: J2.7, U2.5 (DSR0/SCS0/TMS)
/CTS: J2.4, U2.2 (~CTS1)
/MISO/TDO: J2.1, U2.7 (RTS0/MISO/TDO)
/MOSI/TDI: J2.3, U2.8 (TXD0/MOSI/TDI)
/RXD: J2.6, U2.4 (RXD1)
/SCK/TCK: J2.5, U2.6 (CTS0/SCK/TCK)
/SCL: J2.10, U2.11 (RI0/GPIO3/SCL)
/SDA: J2.12, U2.12 (RXD0/SDA)
/TRST: J2.9, U2.9 (TNOW0/DTR0SCS1/TRST)
/TXD: J2.8, U2.3 (TXD1)
/UD+: J1.A6 (D+), J1.B6 (D+), U2.17 (UD+)
/UD-: J1.A7 (D-), J1.B7 (D-), U2.16 (UD-)
GND: C1.2, C2.2, C3.1, C4.1, C5.1, J1.A1 (GND), J1.A12 (GND), J1.B1 (GND), J1.B12 (GND), J1.S1 (SHIELD), J2.11, R1.2, R3.2, R7.2, R8.2, R9.2, U1.2 (GND), U2.18 (GND), Y1.2, Y1.4
unnamed: D1.2 (A), R6.1
unnamed: D1.1 (K), U2.15 (DCD0/GPIO4/ACT)
unnamed: D2.1 (K), R7.1
unnamed: J1.A5 (CC1), R1.1
unnamed: J1.B5 (CC2), R3.1
unnamed: C1.1, J1.A4 (VBUS), J1.A9 (VBUS), J1.B4 (VBUS), J1.B9 (VBUS), U1.1 (VIN), U1.3 (EN)
unnamed: R4.2, R9.1, U2.10 (DTR1/TNOW1)
unnamed: R5.2, R8.1, U2.13 (RTS1/GPIO7)
unnamed: C4.2, U2.19 (XI), Y1.3
unnamed: C5.2, U2.20 (XO), Y1.1
unnamed: C3.2, R2.1, U2.1 (~RST)

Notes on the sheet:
DTR1 RTS1 Function 1 1 USB --> 2 UARTs 1 0 USB --> UART + I2C + SPI 0 1 USB --> UART + I2C + SPI 0 0 USB --> UART + JTAG

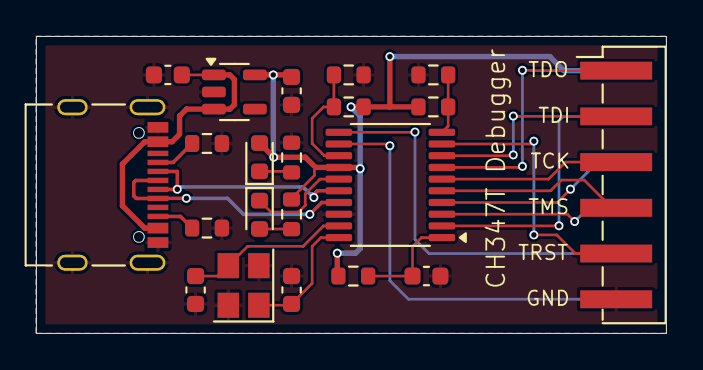
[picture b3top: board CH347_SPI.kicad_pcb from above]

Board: 2 copper layers, 35.0 x 16.5 mm, 21 parts (0 on the bottom side), 25 nets.

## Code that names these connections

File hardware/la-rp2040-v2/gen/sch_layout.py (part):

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    else:
        P(_ref, XD, _y - 9, 0)
# A-side idle levels
P('R40', XA - 4, ROW['U5'] + 9)              # IO0_A pull-down: pin 1 = IO0_A (top), crosses the DIR line
P('R41', XA, ROW['U6'] - 3)
P('R42', XA, ROW['U7'] - 3)
P('R43', XA, ROW['U9'] - 3)
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        P(_ref, XP, _y - 3, 0)
    SPLIT[_net] = [([f'{r}.2' for r in _series[_net]] + [f'{_ref}.2'], (XL, _y, 0))]
NOTES += [(270, 21, 2.5, 'LEVEL-SHIFTED IO0..IO7'),
          (270, 24, 1.5, 'A = 3V3 side, B = VIO side'), (270, 26, 1.5, 'DIR high = probe drives the pin'),
          (XL + 6, 64, 1.3, 'SWCLK (GP12)'), (XL + 6, 88, 1.3, 'SWDIO: out GP14 through 470R, in GP13'),
          (XL + 6, 136, 1.3, 'nRESET (GP20)'), (XL + 6, 160, 1.3, 'UART TX (GP4)'),
          (XL + 6, 184, 1.3, 'UART RX (GP5)'), (XL + 6, 208, 1.3, 'GP23'), (XL + 6, 232, 1.3, 'GP24'),
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P('C31', 288, 290)
NOTES += [(238, 270, 2.5, 'ANALOG INPUTS (clamped to 0..3.3 V) / VIO SENSE')]

# nets that run in the channel, and the pins the channel reaches with a straight horizontal wire
CHANNEL_NETS = ['LED_USB', 'LED_RX', 'LED_TX', 'LED_DAP', 'LED_ACT',
                'IO0_A', 'DIR0', 'SWDIO_O', 'DIR1', 'IO1_A', 'IO2_A', 'DIR2', 'IO3_A', 'DIR3', 'IO4_A', 'DIR4',
                'IO5_A', 'IO6_A', 'IO7_A', 'DIR567', 'ADC0', 'ADC1', 'ADC2', 'VIO_SENSE']
CHANNEL_EXTRA = {'VIO_SENSE': ['R60.2']}        # 2-pin parts entered from the side

# ═══════════════ target connector, protection, VIO, +5 V out ═══════════════
X3 = 336
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

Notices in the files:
parts and their libraries:
Copyright 2021 Accelerated Designs. All rights reserved.
